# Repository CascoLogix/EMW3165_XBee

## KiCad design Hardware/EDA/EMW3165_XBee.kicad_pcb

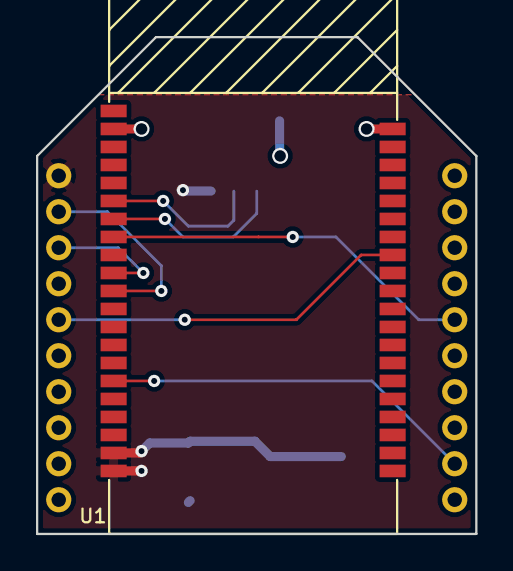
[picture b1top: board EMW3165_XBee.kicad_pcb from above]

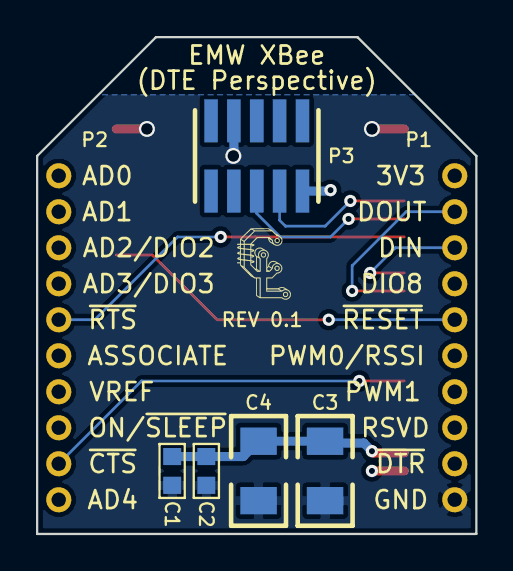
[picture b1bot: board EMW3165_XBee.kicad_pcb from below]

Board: 2 copper layers, 24.4 x 27.6 mm, 8 parts (7 on the bottom side), 9 nets.

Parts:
C1: 0.1uF; 0603
C2: 1uF; 0603
C3, C4: 47uF; 1206
P1: XBEE P1-P10; HEADER_XBEE_P1_P10_ALT3
P2: XBEE P11-P20; HEADER_XBEE_P11_P20_ALT3
P3: JTAG; HEADER_M_1.27MM_2R10P_ST_AU_SMT
U1: EMW3165; EMW3165_SMT

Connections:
3.3V: C1.1, C2.1, C3.1, C4.1, P1.1, P3.2, U1.39, U1.40
GND: C1.2, C2.2, C3.2, C4.2, P1.10, P3.7, U1.20, U1.21
JTCK/SWCLK: P3.4, U1.25
JTMS/SWDIO: P3.6, U1.26
RESET: P1.5, U1.13
USART1_CTS: P2.12, U1.35
USART1_RTS: P2.16, U1.27
USART1_RX: P1.3, U1.29
USART1_TX: P1.2, U1.30

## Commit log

2016-12-05 First commit.
2016-12-09 Finished prototype design and generated gerbers for OSH Park.
2016-12-11 Ordered from OSH Park
